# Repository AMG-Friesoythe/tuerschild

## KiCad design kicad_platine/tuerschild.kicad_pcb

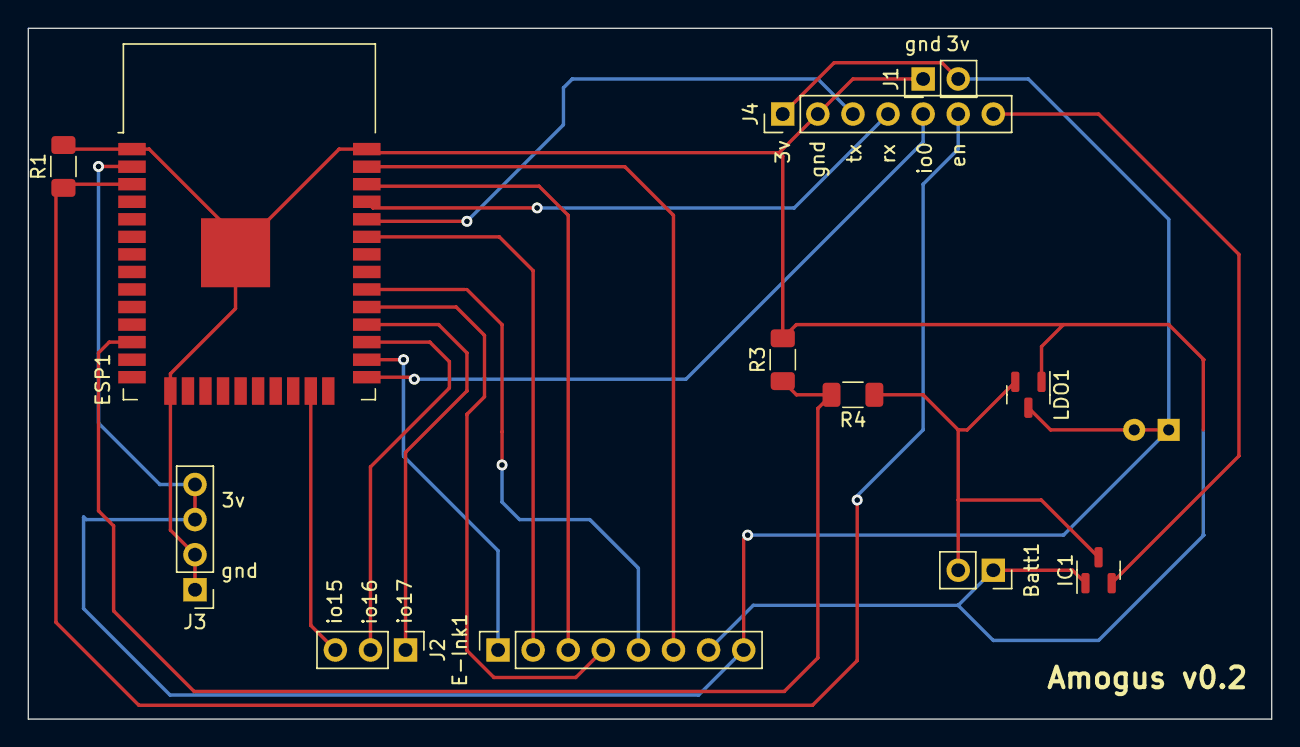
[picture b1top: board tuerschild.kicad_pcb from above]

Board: 2 copper layers, 90.0 x 50.0 mm, 13 parts (1 on the bottom side), 17 nets.

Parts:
Batt1: Conn_01x02_Female; PinSocket_1x02_P2.54mm_Vertical
C1: CP; CP_Radial_D6.3mm_P2.50mm
E-Ink1: Conn_01x08_Female; PinSocket_1x08_P2.54mm_Vertical
ESP1: ESP32-WROOM-32
IC1: SGM809-TXN3L; SOT-23
J1: Jump; PinHeader_1x02_P2.54mm_Vertical
J2: Conn_01x03_Male; PinHeader_1x03_P2.54mm_Vertical
J3: Conn_01x04_Male; PinHeader_1x04_P2.54mm_Vertical
J4: Dev; PinHeader_1x07_P2.54mm_Vertical
LDO1: MCP1700-3002E_SOT-23; SOT-23
R1, R3, R4: R_Small; R_1206_3216Metric_Pad1.30x1.75mm_HandSolder

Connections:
unnamed: Batt1.1, C1.2, E-Ink1.7, ESP1.1 (GND), ESP1.15 (GND), ESP1.38 (GND), ESP1.39 (GND), IC1.1 (GND), J1.1, J3.1, J3.2, J4.2, LDO1.1 (GND), R1.2, R3.2
unnamed: Batt1.2, IC1.3 (VCC), LDO1.2 (VI), R4.1
unnamed: C1.1, E-Ink1.8, ESP1.2 (VDD), J1.2, J3.3, J3.4, J4.1, LDO1.3 (VO)
unnamed: E-Ink1.1, ESP1.26 (IO4)
unnamed: E-Ink1.2, ESP1.33 (IO21)
unnamed: E-Ink1.3, ESP1.36 (IO22)
unnamed: E-Ink1.4, ESP1.29 (IO5)
unnamed: E-Ink1.6, ESP1.37 (IO23)
unnamed: ESP1.3 (EN), J4.6, R1.1
unnamed: ESP1.12 (IO27), R3.1, R4.2
unnamed: ESP1.23 (IO15), J2.3
unnamed: ESP1.25 (IO0), J4.5
unnamed: ESP1.27 (IO16), J2.2
unnamed: ESP1.28 (IO17), J2.1
unnamed: ESP1.34 (RXD0/IO3), J4.3
unnamed: ESP1.35 (TXD0/IO1), J4.4
unnamed: IC1.2 (~RESET/RESET), J4.7

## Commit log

2022-11-11 restructured project
2022-11-11 remove moved files
2022-11-11 project-libs added
2022-11-11 fixup pcb: rerouting, labels
2022-11-12 added server-side php code
2022-11-12 added freecad model for the case; added 3mm height for battery height lifting front plate
2022-11-14 added an excl. mark
